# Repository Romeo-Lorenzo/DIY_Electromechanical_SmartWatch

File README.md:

## Introduction
This is my take at making my own quartz watch with a twist.
Driven by a PCF2003 chip from NXP as well as an STM32WB for bluetooth capability and controlling the subdial driving system in order to display data from the equipped sensors:
- Barometer
- Compass
- VBat
- Temp
- 1 cell lithium charge and discharge
- Very low power circuitry, 150nA continuous current consumption and 150mA with STM32 turned on. Designed to be equipped of two Airpods1 batteries in parralel for 50mAh total.

## Hardware:

  The hardware is divided into electrical and mecanical hardware

  ### Electrical:
  - 6 layer 36mm PCB board designed to replace original PCB from a Miyota 2035 movement. The PCB has two contact pads for two Miyota 2035 movements to drive both main and sub-dial. It is equipped with contact pads to ease programming of both the STM32 and the PCF 2003, most likely with pogo pin alignement 3D print to come.

  - TODO Monolayer PCB to mount as shield on Nucleo board equipped with OP Amp to be able to output the voltage necessary to program the PCF 2003. Will most likely be designed as a programming station and include the pogo pins and debug connector for programming the STM32 as well and be integrated with the forementioned 3d model to print.
 
  ### Mecanical:
  - Onshape designed 36mm watch case with high water resistance in mind, a water tight push button to control subdial and STM32 ON time.
  - 

Note that the Miyota 2035 movements will have to be modified, taking it apart and filing away the excess material on the bottom holding plate for the subdial movement is an easy fit and a tutorial on how to take apart and prepare the movements will be released.
The case is not yet finished but I estimate a 5 atm water tight watch, tolerances for CNC machinig will have to be tested. Crown will be a screw-in watertight type, a silicon membrane will ensure watertightness of the push button all the while allowing the inside barometer to read pressure, especially fun underwater.

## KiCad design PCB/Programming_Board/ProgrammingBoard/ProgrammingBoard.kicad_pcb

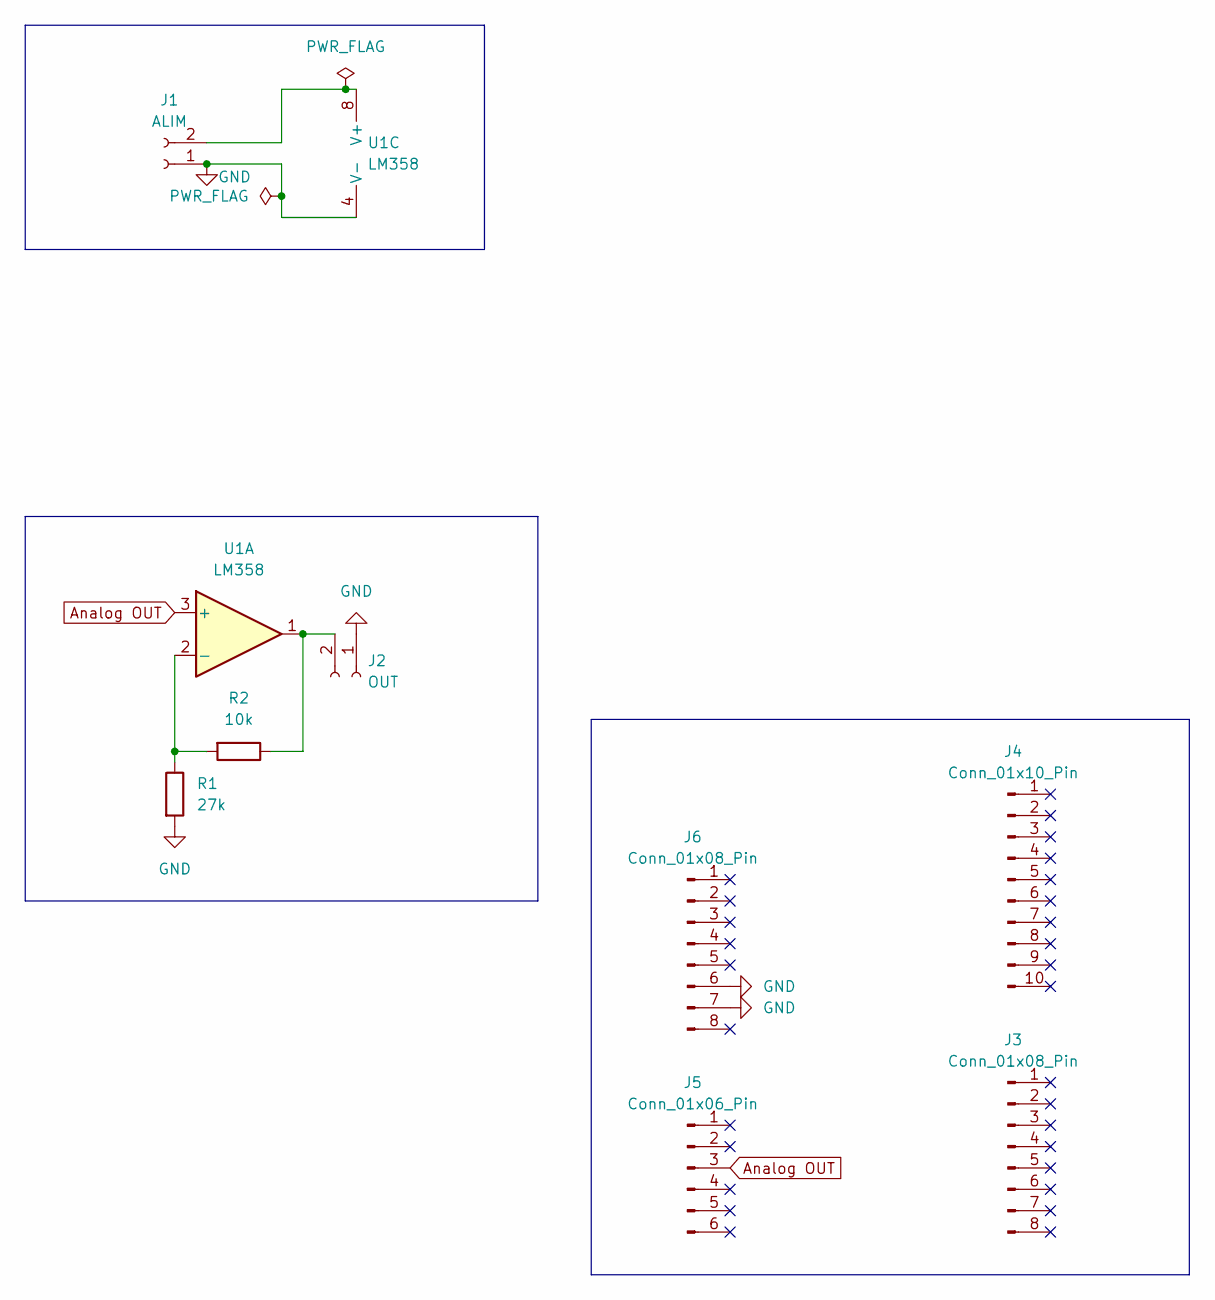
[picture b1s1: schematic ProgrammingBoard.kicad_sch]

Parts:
J1: ALIM; PinSocket_1x02_P2.54mm_Vertical
J2: OUT; PinSocket_1x02_P2.54mm_Vertical
J3, J6: Conn_01x08_Pin; PinHeader_1x08_P2.54mm_Vertical
J4: Conn_01x10_Pin; PinHeader_1x10_P2.54mm_Vertical
J5: Conn_01x06_Pin; PinHeader_1x06_P2.54mm_Vertical
R1: 27k; R_Axial_DIN0204_L3.6mm_D1.6mm_P5.08mm_Horizontal
R2: 10k; R_Axial_DIN0204_L3.6mm_D1.6mm_P5.08mm_Horizontal
U1: LM358; LM358P

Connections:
Analog OUT: J5.3, U1.3 (+)
GND: J1.1, J2.1, J6.6, J6.7, R1.2, U1.4 (V-)
unnamed: J1.2, U1.8 (V+)
unnamed: J2.2, R2.1, U1.1
unnamed: R1.1, R2.2, U1.2 (-)

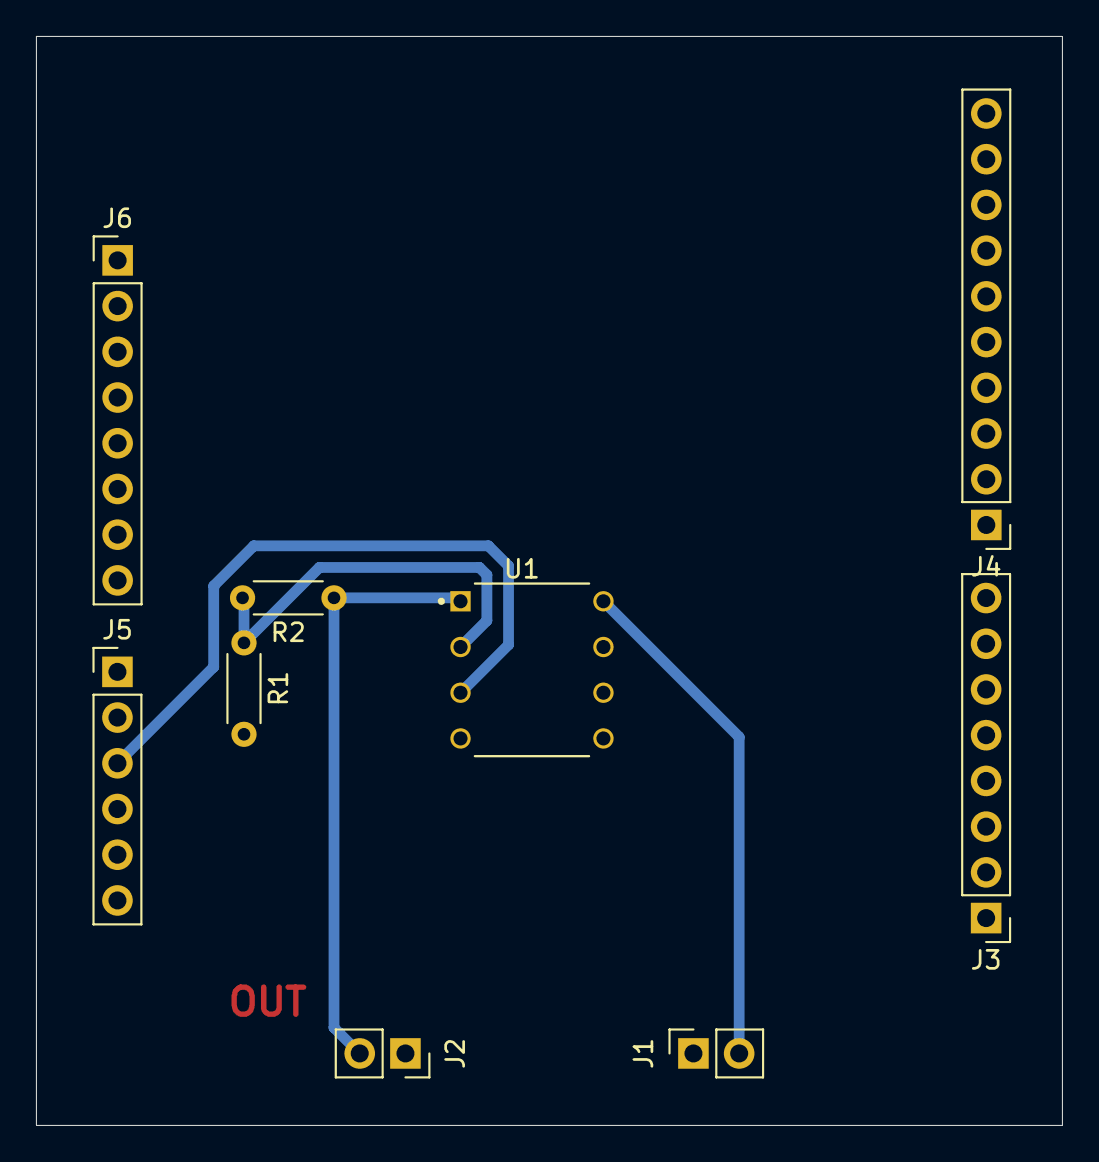
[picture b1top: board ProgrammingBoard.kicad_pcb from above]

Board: 2 copper layers, 57.0 x 60.5 mm, 9 parts (0 on the bottom side), 5 nets.

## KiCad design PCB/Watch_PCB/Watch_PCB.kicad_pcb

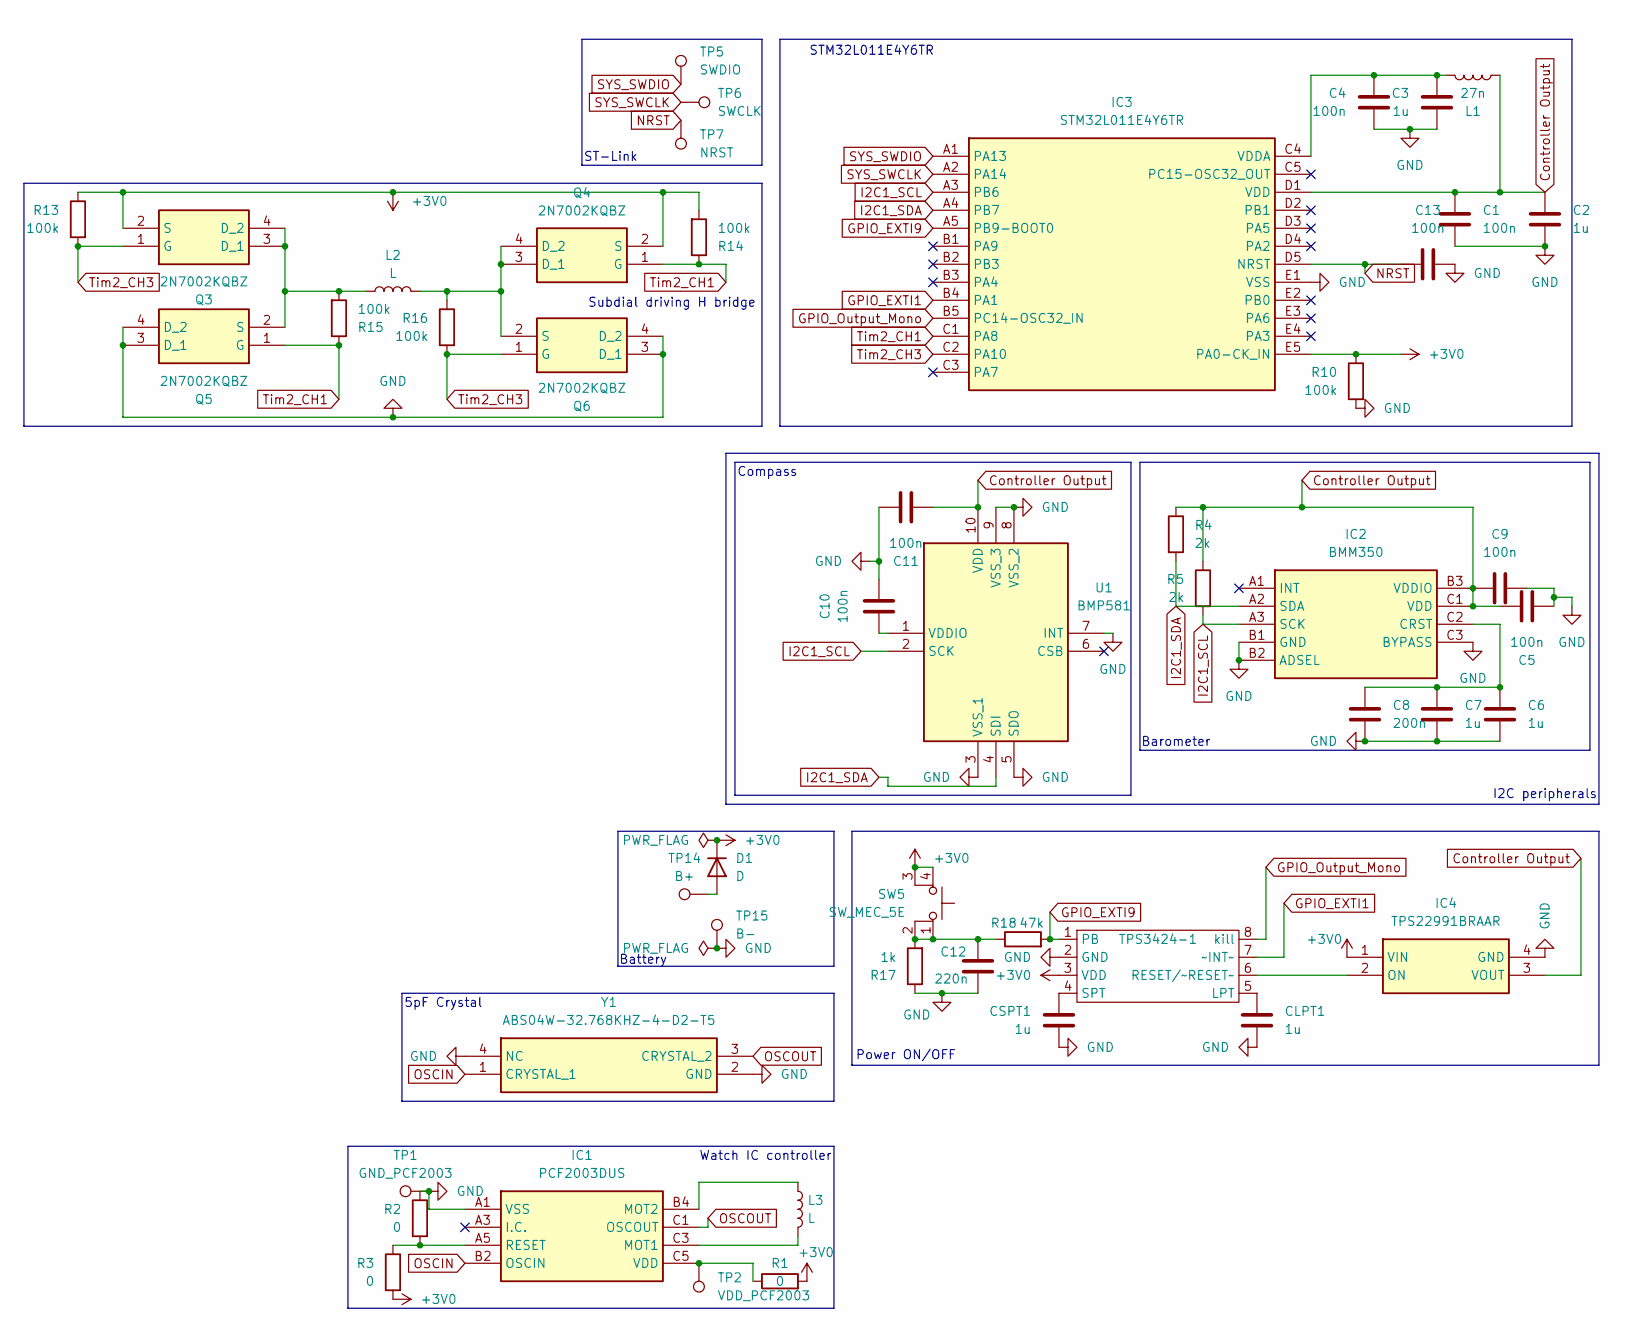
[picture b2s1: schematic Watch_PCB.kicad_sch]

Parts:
C1, C4, C5, C9, C10, C11, C13: 100n; C_0201_0603Metric
C2, C3, C6, C7: 1u; C_0201_0603Metric
C8: 200n; C_0201_0603Metric
C12: 220n; C_0201_0603Metric
CLPT1: 1u; C_0201_0603Metric
CSPT1: 1u; C_0201_0603Metric
D1: D; D_0201_0603Metric
IC1: PCF2003DUS; Manufacturer_Part_Number PCF2003DUS
IC2: BMM350; BGA9C40P3X3_128X128X54; Mouser Part Number 262-BMM350
IC3: STM32L011E4Y6TR; BGA25C40P5X5_213X207X58; Manufacturer_Part_Number STM32L011E4Y6TR; Mouser Part Number 511-STM32L011E4Y6TR
IC4: TPS22991BRAAR; Manufacturer_Part_Number TPS22991BRAAR; Mouser Part Number 595-TPS22991BRAAR
L1: 27n; L_0201_0603Metric
L2, L3: L; Miyota 2035
Q3, Q4, Q5, Q6: 2N7002KQBZ; Manufacturer_Part_Number 2N7002KQBZ; Mouser Part Number 771-2N7002KQBZ
R1, R2, R3: 0; R_0201_0603Metric
R4, R5: 2k; R_0201_0603Metric
R10, R13, R14, R15, R16: 100k; R_0201_0603Metric
R17: 1k; R_0201_0603Metric
R18: 47k; R_0201_0603Metric
SW5: SW_MEC_5E; Wurth side button 434331013822
TP1: GND_PCF2003; TestPoint_Pad_D1.0mm
TP2: VDD_PCF2003; TestPoint_Pad_D1.0mm
TP5: SWDIO; TestPoint_Pad_D1.0mm
TP6: SWCLK; TestPoint_Pad_D1.0mm
TP7: NRST; TestPoint_Pad_D1.0mm
TP14: B+; TestPoint_Pad_D1.0mm
TP15: B-; TestPoint_Pad_D1.0mm
TPS3424-1: SOT-583-8
U1: BMP581; Manufacturer_Part_Number BMP581; Mouser Part Number 262-BMP581
Y1: ABS04W-32.768KHZ-4-D2-T5; ABS04W32768KHZ4D2T5; Manufacturer_Part_Number ABS04W-32.768KHZ-4-D2-T5; Mouser Part Number 815-04W-32.768-4-D2T

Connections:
+3V0: D1.1 (K), IC3.E5 (PA0-CK_IN), IC4.1 (VIN), Q3.2 (S), Q4.2 (S), R1.2, R3.2, R10.1, R13.1, R14.2, SW5.3 (K), SW5.4 (A), TPS3424-1.3 (VDD)
Controller Output: C1.2, C2.2, C5.1, C9.1, C11.2, IC2.B3 (VDDIO), IC2.C1 (VDD), IC3.D1 (VDD), IC4.3 (VOUT), L1.1, R4.1, R5.1, U1.10 (VDD)
GND: C1.1, C2.1, C3.1, C4.1, C5.2, C6.2, C7.2, C8.2, C9.2, C10.1, C11.1, C12.1, C13.2, CLPT1.1, CSPT1.1, IC1.A1 (VSS), IC2.B1 (GND), IC2.B2 (ADSEL), IC2.C3 (BYPASS), IC3.E1 (VSS), IC4.4 (GND), Q5.3 (D_1), Q5.4 (D_2), Q6.3 (D_1), Q6.4 (D_2), R2.1, R10.2, R17.1, TP1.1, TP15.1, TPS3424-1.2 (GND), U1.3 (VSS_1), U1.5 (SDO), U1.7 (INT), U1.8 (VSS_2), U1.9 (VSS_3), Y1.2 (GND), Y1.4 (NC)
GPIO_EXTI1: IC3.B4 (PA1), TPS3424-1.7 (~INT~)
GPIO_EXTI9: IC3.A5 (PB9-BOOT0), R18.2, TPS3424-1.1 (PB)
GPIO_Output_Mono: IC3.B5 (PC14-OSC32_IN), TPS3424-1.8 (kill)
I2C1_SCL: IC2.A3 (SCK), IC3.A3 (PB6), R5.2, U1.2 (SCK)
I2C1_SDA: IC2.A2 (SDA), IC3.A4 (PB7), R4.2, U1.4 (SDI)
NRST: C13.1, IC3.D5 (NRST), TP7.1
unnamed: C12.2, R17.2, R18.1, SW5.1, SW5.2
unnamed: D1.2 (A), TP14.1
unnamed: IC1.C3 (MOT1), L3.2
unnamed: IC1.B4 (MOT2), L3.1
unnamed: IC1.A5 (RESET), R2.2, R3.1
unnamed: IC1.C5 (VDD), R1.1, TP2.1
unnamed: C6.1, C7.1, C8.1, IC2.C2 (CRST)
unnamed: C3.2, C4.2, IC3.C4 (VDDA), L1.2
unnamed: IC4.2 (ON), TPS3424-1.6 (RESET/~RESET~)
unnamed: L2.1, Q3.3 (D_1), Q3.4 (D_2), Q5.2 (S), R15.2
unnamed: L2.2, Q4.3 (D_1), Q4.4 (D_2), Q6.2 (S), R16.1
unnamed: CLPT1.2, TPS3424-1.5 (LPT)
unnamed: CSPT1.2, TPS3424-1.4 (SPT)
unnamed: C10.2, U1.1 (VDDIO)
OSCIN: IC1.B2 (OSCIN), Y1.1 (CRYSTAL_1)
OSCOUT: IC1.C1 (OSCOUT), Y1.3 (CRYSTAL_2)
SYS_SWCLK: IC3.A2 (PA14), TP6.1
SYS_SWDIO: IC3.A1 (PA13), TP5.1
Tim2_CH1: IC3.C1 (PA8), Q4.1 (G), Q5.1 (G), R14.1, R15.1
Tim2_CH3: IC3.C2 (PA10), Q3.1 (G), Q6.1 (G), R13.2, R16.2

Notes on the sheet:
5pF Crystal
ST-Link
Power ON/OFF
Subdial driving H bridge
Compass
Watch IC controller
I2C peripherals
Barometer
Battery
STM32L011E4Y6TR

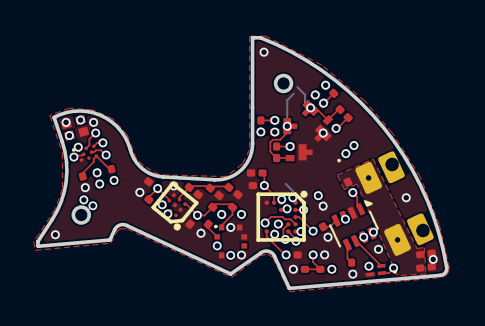
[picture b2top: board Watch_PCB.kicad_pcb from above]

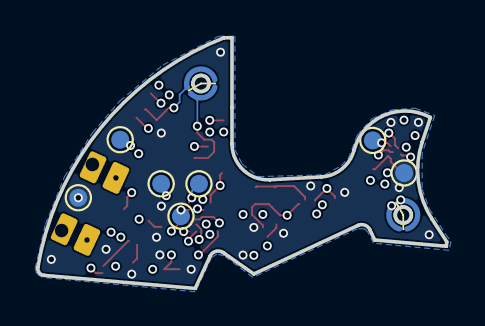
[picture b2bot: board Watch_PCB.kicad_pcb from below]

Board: 6 copper layers, 22.7 x 13.9 mm, 50 parts (9 on the bottom side), 29 nets.

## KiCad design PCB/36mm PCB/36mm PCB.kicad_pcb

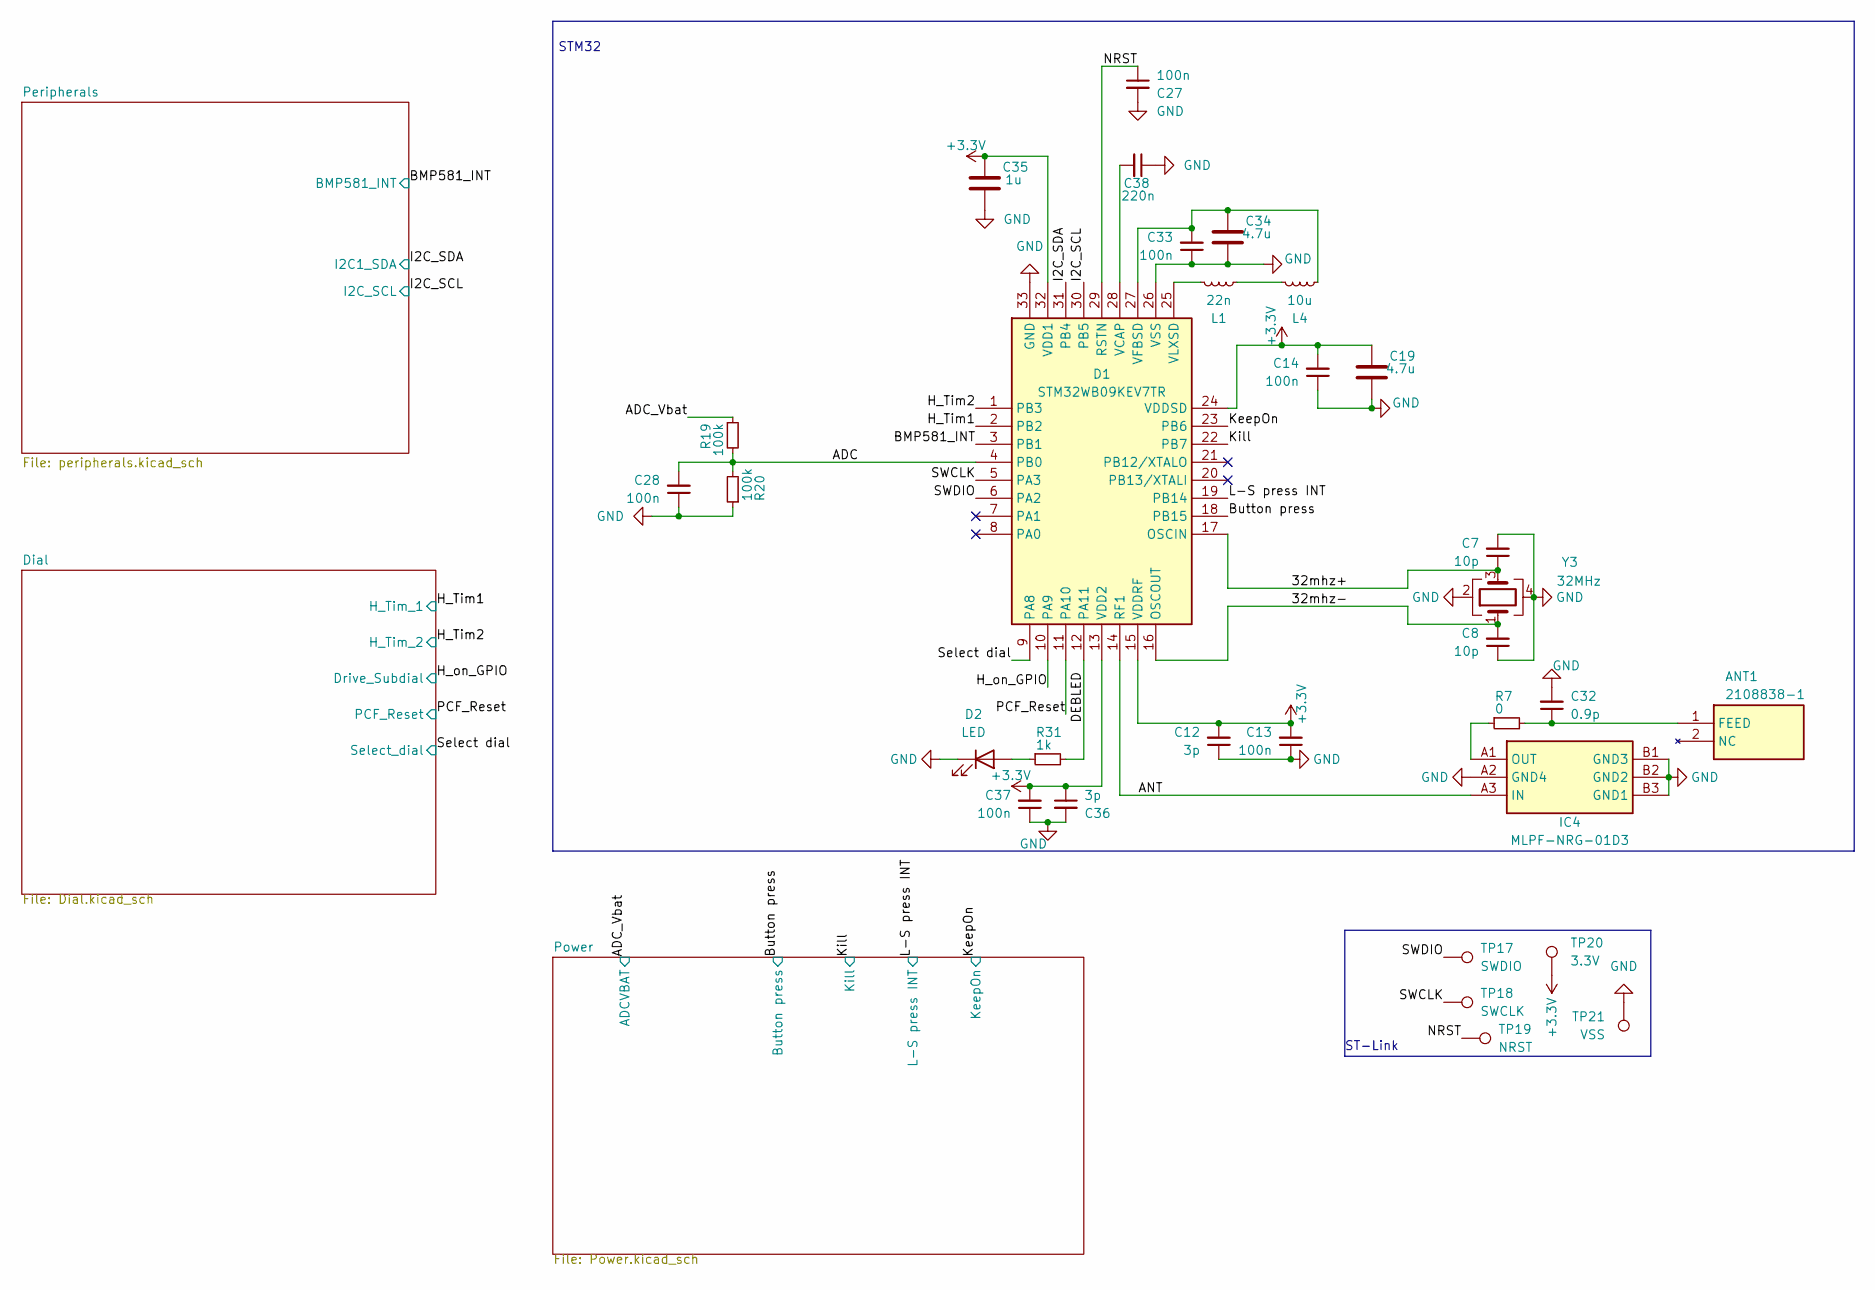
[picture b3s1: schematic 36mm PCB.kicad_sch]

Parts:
ANT1: 2108838-1; ANTC3216X140N; Manufacturer_Part_Number 2108838-1; Mouser Part Number 571-2108838-1
C7, C8: 10p; C_0201_0603Metric
C12, C36: 3p; C_0201_0603Metric
C13, C14, C27, C28, C33, C37: 100n; C_0201_0603Metric
C19, C34: 4.7u; C_0402_1005Metric
C32: 0.9p; C_0201_0603Metric
C35: 1u; C_0402_1005Metric
C38: 220n; C_0201_0603Metric
D1: STM32WB09KEV7TR; QFN50P500X500X100-33N-D; Manufacturer_Part_Number STM32WB09KEV7TR; Mouser Part Number 511-STM32WB09KEV7TR
D2: LED; LED_0402_1005Metric
IC4: MLPF-NRG-01D3; CSPG_2025; Manufacturer_Part_Number MLPF-NRG-01D3; Mouser Part Number 511-MLPF-NRG-01D3
L1: 22n; L_0402_1005Metric
L4: 10u; L_0805_2012Metric
R7: 0; R_0201_0603Metric
R19, R20: 100k; R_0201_0603Metric
R31: 1k; R_0201_0603Metric
TP17: SWDIO; Pogo pin 1x1
TP18: SWCLK; Pogo pin 1x1
TP19: NRST; Pogo pin 1x1
TP20: 3.3V; Pogo pin 1x1
TP21: VSS; Pogo pin 1x1
Y3: 32MHz; LFXTAL069526

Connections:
+3.3V: C12.2, C13.2, C14.2, C19.1, C35.1, C36.1, C37.2, D1.13 (VDD2), D1.15 (VDDRF), D1.24 (VDDSD), D1.32 (VDD1), TP20.1; also elsewhere on the board
+3V0: R19.1; also elsewhere on the board
/32mhz+: C7.1, D1.17 (OSCIN), Y3.3
/32mhz-: C8.2, D1.16 (OSCOUT), Y3.1
/ADC: C28.2, D1.4 (PB0), R19.2, R20.2
/ANT: D1.14 (RF1), IC4.A3 (IN)
/BMP581_INT: D1.3 (PB1); also elsewhere on the board
/Button press: D1.18 (PB15); also elsewhere on the board
/DEBLED: D1.12 (PA11), R31.2
/H_Tim1: D1.2 (PB2); also elsewhere on the board
/H_Tim2: D1.1 (PB3); also elsewhere on the board
/H_on_GPIO: D1.10 (PA9); also elsewhere on the board
/I2C_SCL: D1.30 (PB5); also elsewhere on the board
/I2C_SDA: D1.31 (PB4); also elsewhere on the board
/KeepOn: D1.23 (PB6); also elsewhere on the board
/Kill: D1.22 (PB7); also elsewhere on the board
/L-S press INT: D1.19 (PB14); also elsewhere on the board
/NRST: C27.1, D1.29 (RSTN), TP19.1
/PCF_Reset: D1.11 (PA10); also elsewhere on the board
/SWCLK: D1.5 (PA3), TP18.1
/SWDIO: D1.6 (PA2), TP17.1
/Select dial: D1.9 (PA8); also elsewhere on the board
GND: C7.2, C8.1, C12.1, C13.1, C14.1, C19.2, C27.2, C28.1, C32.2, C33.1, C34.2, C35.2, C36.2, C37.1, C38.1, D1.26 (VSS), D1.33 (GND), D2.1 (K), IC4.A2 (GND4), IC4.B1 (GND3), IC4.B2 (GND2), IC4.B3 (GND1), R20.1, TP21.1, Y3.2, Y3.4; also elsewhere on the board
unnamed: ANT1.1 (FEED), C32.1, R7.2
unnamed: C38.2, D1.28 (VCAP)
unnamed: C33.2, C34.1, D1.27 (VFBSD), L4.2
unnamed: D1.25 (VLXSD), L1.1
unnamed: D2.2 (A), R31.1
unnamed: IC4.A1 (OUT), R7.1
unnamed: L1.2, L4.1

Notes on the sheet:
ST-Link
STM32

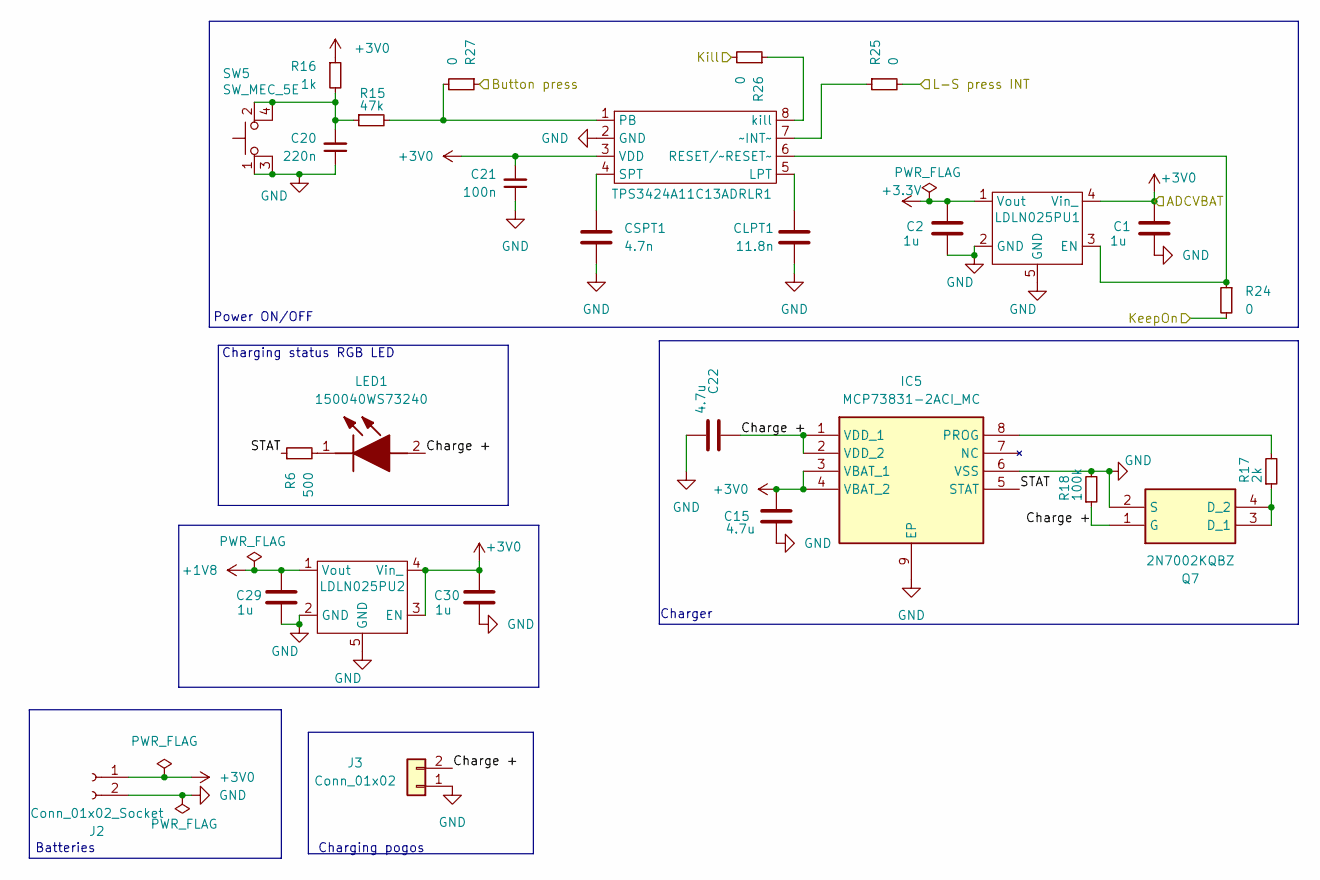
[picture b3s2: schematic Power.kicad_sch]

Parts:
C1, C2, C29, C30: 1u; C_0402_1005Metric
C15, C22: 4.7u; C_0402_1005Metric
C20: 220n; C_0201_0603Metric
C21: 100n; C_0201_0603Metric
CLPT1: 11.8n; C_0201_0603Metric
CSPT1: 4.7n; C_0201_0603Metric
IC5: MCP73831-2ACI_MC; SON50P300X200X100-9N-D; Manufacturer_Part_Number MCP73831-2ACI/MC; Mouser Part Number 579-MCP73831-2ACI/MC
J2: Conn_01x02_Socket; Battery 36mm watch
J3: Conn_01x02; Battery pogo pins
LDLN025PU1, LDLN025PU2: OnSemi_XDFN4-1EP_1.0x1.0mm_EP0.52x0.52mm
LED1: 150040WS73240; Manufacturer_Part_Number 150040WS73240; Mouser Part Number 710-150040WS73240
Q7: 2N7002KQBZ; Manufacturer_Part_Number 2N7002KQBZ; Mouser Part Number 771-2N7002KQBZ
R6: 500; R_0201_0603Metric
R15: 47k; R_0201_0603Metric
R16: 1k; R_0201_0603Metric
R17: 2k; R_0201_0603Metric
R18: 100k; R_0201_0603Metric
R24, R25, R26, R27: 0; R_0201_0603Metric
SW5: SW_MEC_5E; Wurth side button 434331013822
TPS3424A11C13ADRLR1: SOT-583-8

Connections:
+1V8: C29.1, LDLN025PU2.1 (Vout); also elsewhere on the board
+3.3V: C2.1, LDLN025PU1.1 (Vout); also elsewhere on the board
+3V0: C1.1, C15.1, C21.2, C30.1, IC5.3 (VBAT_1), IC5.4 (VBAT_2), J2.1, LDLN025PU1.4 (Vin_), LDLN025PU2.3 (EN), LDLN025PU2.4 (Vin_), R16.1, TPS3424A11C13ADRLR1.3 (VDD); also elsewhere on the board
/Button press: R27.1; also elsewhere on the board
/KeepOn: R24.2; also elsewhere on the board
/Kill: R26.2; also elsewhere on the board
/L-S press INT: R25.2; also elsewhere on the board
/Power/Charge +: C22.1, IC5.1 (VDD_1), IC5.2 (VDD_2), J3.2, LED1.2 (A), Q7.1 (G), R18.1
/Power/STAT: IC5.5 (STAT), R6.1
GND: C1.2, C2.2, C15.2, C20.1, C21.1, C22.2, C29.2, C30.2, CLPT1.1, CSPT1.1, IC5.6 (VSS), IC5.9 (EP), J2.2, J3.1, LDLN025PU1.2 (GND), LDLN025PU1.5 (GND), LDLN025PU2.2 (GND), LDLN025PU2.5 (GND), Q7.2 (S), R18.2, SW5.1, SW5.3, TPS3424A11C13ADRLR1.2 (GND); also elsewhere on the board
unnamed: C20.2, R15.1, R16.2, SW5.2, SW5.4
unnamed: IC5.8 (PROG), R17.2
unnamed: LDLN025PU1.3 (EN), R24.1, TPS3424A11C13ADRLR1.6 (RESET/~RESET~)
unnamed: LED1.1 (K), R6.2
unnamed: Q7.3 (D_1), Q7.4 (D_2), R17.1
unnamed: CLPT1.2, TPS3424A11C13ADRLR1.5 (LPT)
unnamed: R15.2, R27.2, TPS3424A11C13ADRLR1.1 (PB)
unnamed: CSPT1.2, TPS3424A11C13ADRLR1.4 (SPT)
unnamed: R26.1, TPS3424A11C13ADRLR1.8 (kill)
unnamed: R25.1, TPS3424A11C13ADRLR1.7 (~INT~)

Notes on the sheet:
Charging pogos
Charging status RGB LED
Charger
Batteries
Power ON/OFF

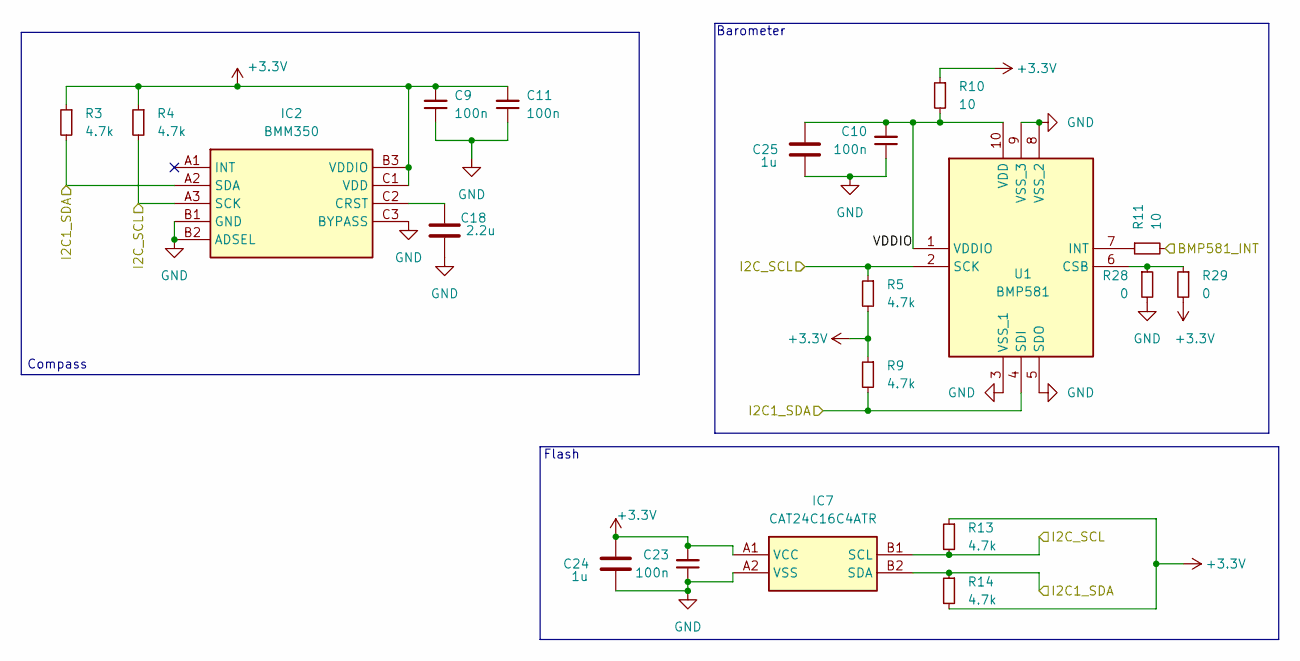
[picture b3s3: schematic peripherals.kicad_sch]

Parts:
C9, C10, C11, C23: 100n; C_0201_0603Metric
C18: 2.2u; C_0402_1005Metric
C24, C25: 1u; C_0402_1005Metric
IC2: BMM350; BGA9C40P3X3_128X128X54; Mouser Part Number 262-BMM350
IC7: CAT24C16C4ATR; BGA4C40P2X2_84X84X38; Manufacturer_Part_Number CAT24C16C4ATR; Mouser Part Number 863-CAT24C16C4ATR
R3, R4, R5, R9, R13, R14: 4.7k; R_0201_0603Metric
R10, R11: 10; R_0201_0603Metric
R28, R29: 0; R_0201_0603Metric
U1: BMP581; Manufacturer_Part_Number BMP581; Mouser Part Number 262-BMP581

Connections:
+3.3V: C9.2, C11.2, C23.2, C24.1, IC2.B3 (VDDIO), IC2.C1 (VDD), IC7.A1 (VCC), R3.1, R4.1, R5.2, R9.1, R10.1, R13.1, R14.2, R29.2; also elsewhere on the board
/BMP581_INT: R11.2; also elsewhere on the board
/I2C_SCL: IC2.A3 (SCK), IC7.B1 (SCL), R4.2, R5.1, R13.2, U1.2 (SCK); also elsewhere on the board
/I2C_SDA: IC2.A2 (SDA), IC7.B2 (SDA), R3.2, R9.2, R14.1, U1.4 (SDI); also elsewhere on the board
/Peripherals/VDDIO: C10.2, C25.1, R10.2, U1.1 (VDDIO), U1.10 (VDD)
GND: C9.1, C10.1, C11.1, C18.2, C23.1, C24.2, C25.2, IC2.B1 (GND), IC2.B2 (ADSEL), IC2.C3 (BYPASS), IC7.A2 (VSS), R28.2, U1.3 (VSS_1), U1.5 (SDO), U1.8 (VSS_2), U1.9 (VSS_3); also elsewhere on the board
unnamed: C18.1, IC2.C2 (CRST)
unnamed: R28.1, R29.1, U1.6 (CSB)
unnamed: R11.1, U1.7 (INT)

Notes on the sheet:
Flash
Barometer
Compass

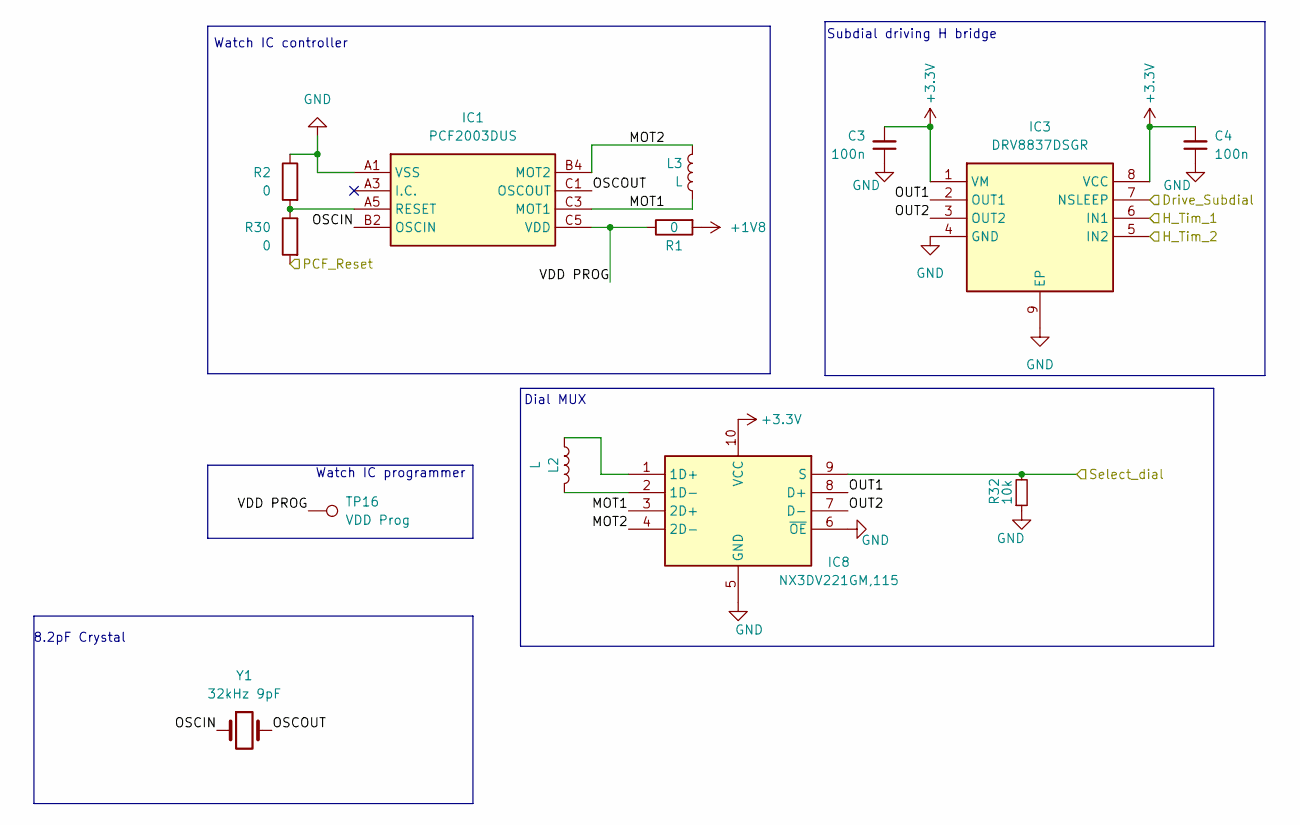
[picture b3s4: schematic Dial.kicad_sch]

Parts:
C3, C4: 100n; C_0201_0603Metric
IC1: PCF2003DUS; Manufacturer_Part_Number PCF2003DUS
IC3: DRV8837DSGR; SON50P200X200X80-9N; Manufacturer_Part_Number DRV8837DSGR; Mouser Part Number 595-DRV8837DSGR
IC8: NX3DV221GM,115; NX3DV221GM115; Manufacturer_Part_Number NX3DV221GM,115; Mouser Part Number 771-NX3DV221GM115
L2, L3: L; Miyota 2035
R1, R2, R30: 0; R_0201_0603Metric
R32: 10k; R_0201_0603Metric
TP16: VDD Prog; Pogo pin 1x1
Y1: 32kHz 9pF; LFXTAL062558Reel

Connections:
+1V8: R1.2; also elsewhere on the board
+3.3V: C3.2, C4.2, IC3.1 (VM), IC3.8 (VCC), IC8.10 (VCC); also elsewhere on the board
/Dial/MOT1: IC1.C3 (MOT1), IC8.3 (2D+), L3.2
/Dial/MOT2: IC1.B4 (MOT2), IC8.4 (2D-), L3.1
/Dial/OSCIN: IC1.B2 (OSCIN), Y1.1
/Dial/OSCOUT: IC1.C1 (OSCOUT), Y1.2
/Dial/OUT1: IC3.2 (OUT1), IC8.8 (D+)
/Dial/OUT2: IC3.3 (OUT2), IC8.7 (D-)
/Dial/VDD PROG: IC1.C5 (VDD), R1.1, TP16.1
/H_Tim1: IC3.6 (IN1); also elsewhere on the board
/H_Tim2: IC3.5 (IN2); also elsewhere on the board
/H_on_GPIO: IC3.7 (NSLEEP); also elsewhere on the board
/PCF_Reset: R30.2; also elsewhere on the board
/Select dial: IC8.9 (S), R32.2; also elsewhere on the board
GND: C3.1, C4.1, IC1.A1 (VSS), IC3.4 (GND), IC3.9 (EP), IC8.5 (GND), IC8.6 (~OE), R2.1, R32.1; also elsewhere on the board
unnamed: IC1.A5 (RESET), R2.2, R30.1
unnamed: IC8.1 (1D+), L2.2
unnamed: IC8.2 (1D-), L2.1

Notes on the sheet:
Watch IC programmer
Watch IC controller
Dial MUX
8.2pF Crystal
Subdial driving H bridge

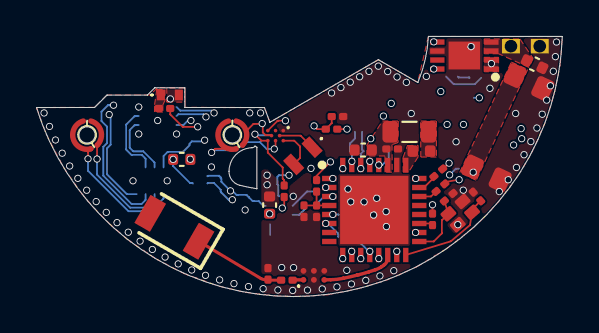
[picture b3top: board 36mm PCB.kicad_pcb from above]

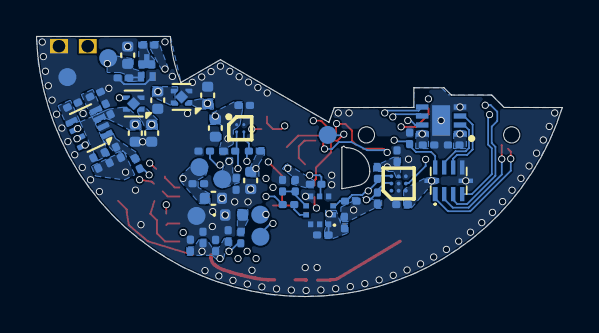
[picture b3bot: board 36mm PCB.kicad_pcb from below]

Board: 6 copper layers, 29.2 x 14.5 mm, 92 parts (59 on the bottom side), 57 nets.

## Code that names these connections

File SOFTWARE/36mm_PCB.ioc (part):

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Mcu.Name=STM32WB09KEVx
Mcu.Package=VFQFPN32
Mcu.UserName=STM32WB09KEVx
PA0.Signal=S_TIM2_CH3
PA1.Signal=S_TIM2_CH4
PA2.Mode=Serial_Wire
PA2.Signal=DEBUG_SWDIO
PA3.Mode=Serial_Wire
PA3.Signal=DEBUG_SWCLK
PA8.Signal=GPIO_Output
PB12.Mode=LSE-External-Oscillator
PB12.Signal=RCC_OSC32_OUT
PB13.Mode=LSE-External-Oscillator
PB13.Signal=RCC_OSC32_IN
PB14.Signal=GPXTI14
PB15.Signal=GPXTI15
PB6.Signal=GPIO_Output
PB7.Signal=GPIO_Output
RCC.HSE_VALUE=32000000
board=custom

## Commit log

2025-11-04 Old repo recovery
    Issue with original repository, header not found
2025-11-04 Update README with project introduction and hardware info
    Expanded project description and hardware details for the DIY Quartz Watch.
2025-11-04 Update README with additional watch images
    Added renders of the 36mm watch design and assembly views.
2025-11-04 file system and pictures
2025-11-04 Revise image links in README.mdcorrect image linking for pdf
    Updated image links to point to the new repository location and removed outdated images. export
2025-11-04 Fix image links in README for proper rendering
    Updated image links in README to use raw URLs for proper display.
